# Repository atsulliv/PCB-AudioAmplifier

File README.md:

## Audio Amplifier (AC-DC Converter + Boombox)

This is a complete audio amplification system, integrating an AC–DC power supply with a class D audio amplifier that drives a passive speaker. Implemented rectification, filtering, and voltage regulation (shunting, transistor stage) to convert wall AC into a stable, adjustable DC rail. Designed the amplifier stage to achieve sufficient gain and output power while maintaining signal fidelity and minimizing harmonic distortion. Extended this project by integrates both the converter and amplifier into a single, two-sided PCB.

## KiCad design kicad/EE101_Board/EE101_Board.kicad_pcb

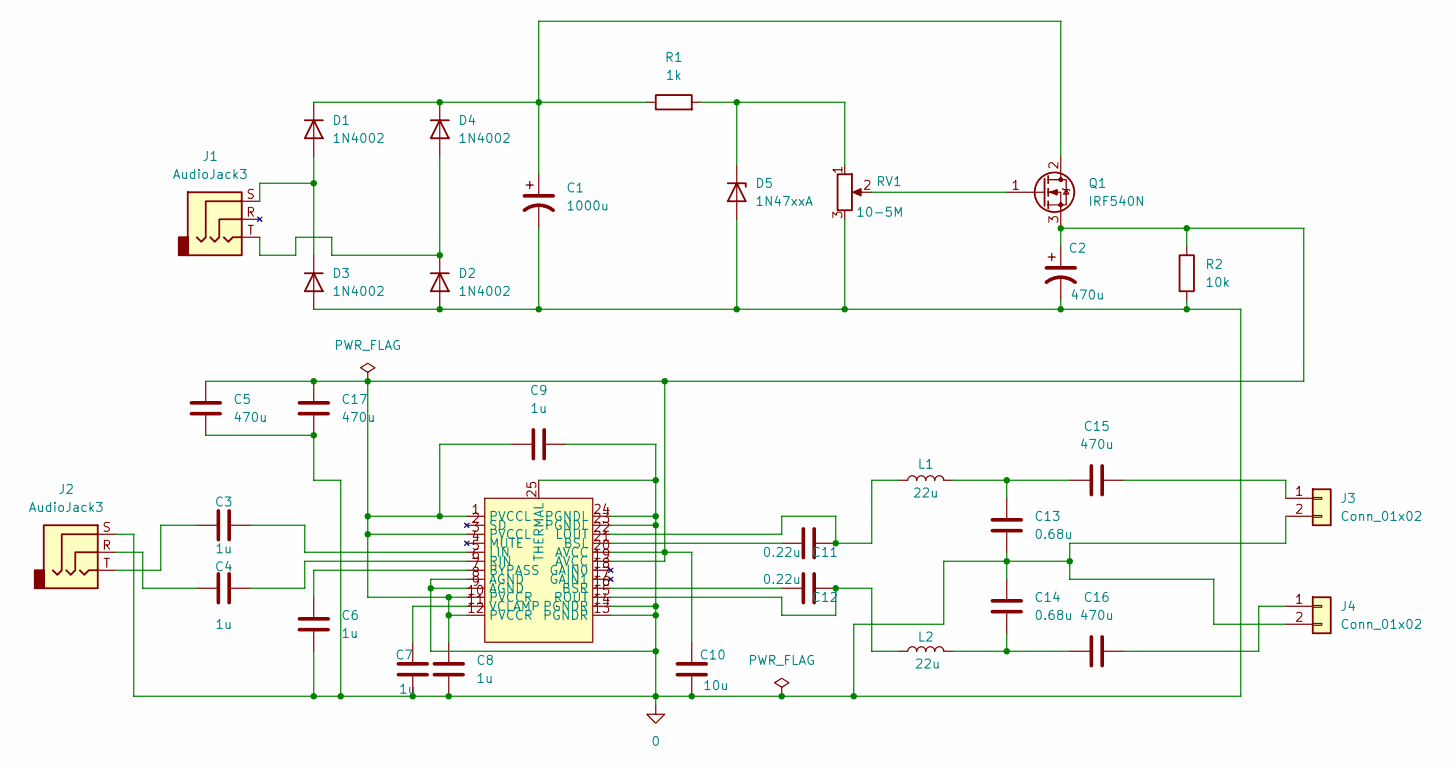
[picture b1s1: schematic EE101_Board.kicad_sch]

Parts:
C1: 1000u; CAPAE1600X1700N
C2: 470u; C-MAL216099003E3
C3, C4, C6, C7, C8, C9: 1u; C_1206_3216Metric_Pad1.33x1.80mm_HandSolder
C5, C15, C16, C17: 470u; Panasonic 25SVPG470M
C10: 10u; C_1206_3216Metric_Pad1.33x1.80mm_HandSolder
C11, C12: 0.22u; C_0603_1608Metric_Pad1.08x0.95mm_HandSolder
C13, C14: 0.68u; C_0805_2012Metric_Pad1.18x1.45mm_HandSolder
D1, D2, D3, D4: 1N4002; D_DO-41_SOD81_P10.16mm_Horizontal
D5: 1N47xxA; DIOM5226X240N
J1, J2: AudioJack3; CUI_SJ-3523-SMT-TR
J3, J4: Conn_01x02; 2249290002
L1, L2: 22u; SRP1038WA220M
Q1: IRF540N; D2PAK-IRF940N
R1: 1k; RESC5025X70N
R2: 10k; R_1206_3216Metric_Pad1.30x1.75mm_HandSolder
RV1: 10-5M; TRIM_3362P-1-205LF
U1: TPA-3123D2-TSSOP - 1.2 mm max height

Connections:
0: C1.2, C2.2, C5.2, C6.2, C7.2, C8.2, C9.2, C10.2, C13.2, C14.1, C17.2, D2.2 (A), D3.2 (A), D5.2 (A), J2.S, J3.2, J4.2, R2.2, RV1.3, U1.8 (AGND), U1.9 (AGND), U1.13 (PGNDR), U1.14 (PGNDR), U1.23 (PGNDL), U1.24 (PGNDL), U1.25 (THERMAL)
unnamed: C3.1, J2.T
unnamed: C4.1, J2.R
unnamed: C13.1, C15.1, L1.2
unnamed: C14.2, C16.1, L2.2
unnamed: D1.2 (A), D3.1 (K), J1.S
unnamed: C1.1, D1.1 (K), D4.1 (K), Q1.2 (D), R1.1
unnamed: D2.1 (K), D4.2 (A), J1.T
unnamed: D5.1 (K), R1.2, RV1.1
unnamed: C15.2, J3.1
unnamed: C16.2, J4.1
unnamed: Q1.1 (G), RV1.2
unnamed: C2.1, C5.1, C8.1, C9.1, C10.1, C17.1, Q1.3 (S), R2.1, U1.1 (PVCCL), U1.3 (PVCCL), U1.10 (PVCCR), U1.12 (PVCCR), U1.19 (AVCC), U1.20 (AVCC)
unnamed: C11.1, U1.21 (BSL)
unnamed: C12.1, U1.16 (BSR)
unnamed: C6.1, U1.7 (BYPASS)
unnamed: C3.2, U1.5 (LIN)
unnamed: C11.2, L1.1, U1.22 (LOUT)
unnamed: C4.2, U1.6 (RIN)
unnamed: C12.2, L2.1, U1.15 (ROUT)
unnamed: C7.1, U1.11 (VCLAMP)

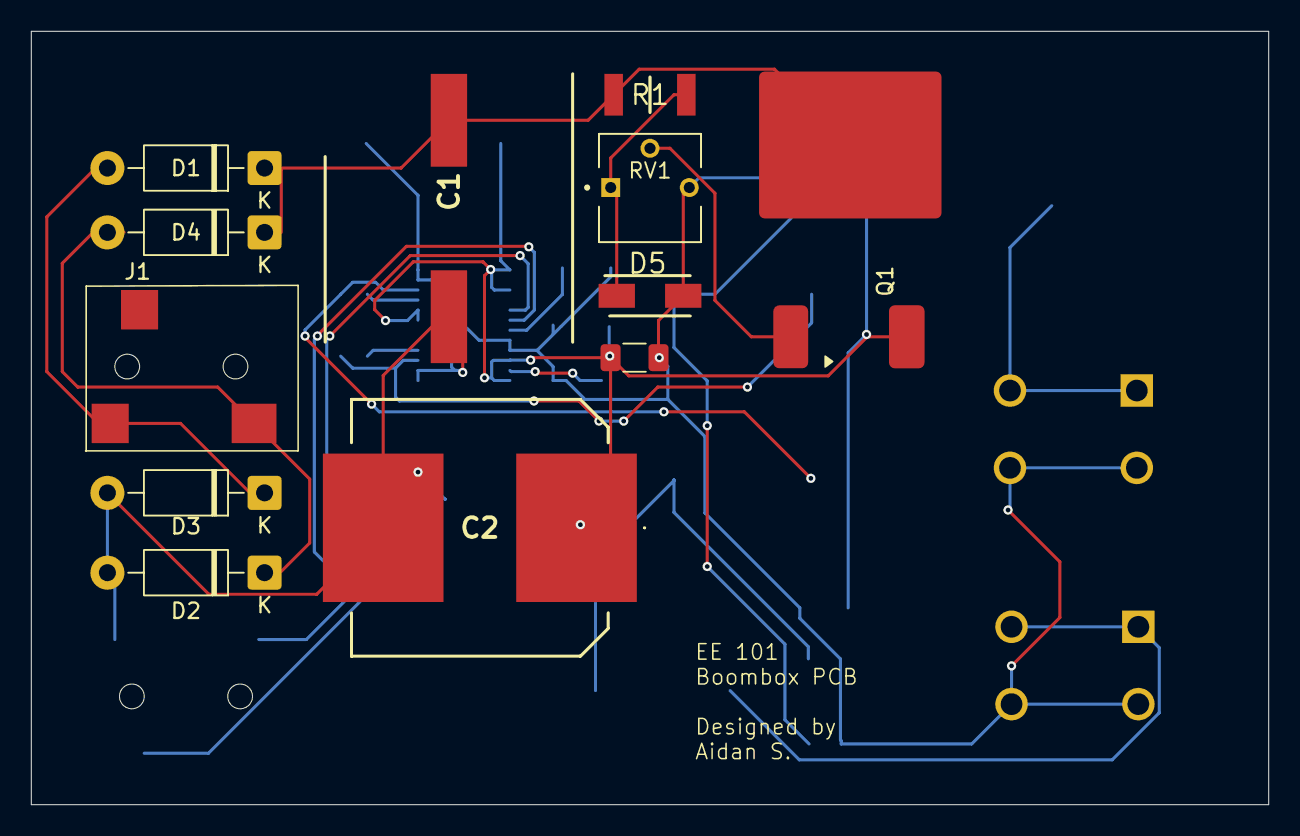
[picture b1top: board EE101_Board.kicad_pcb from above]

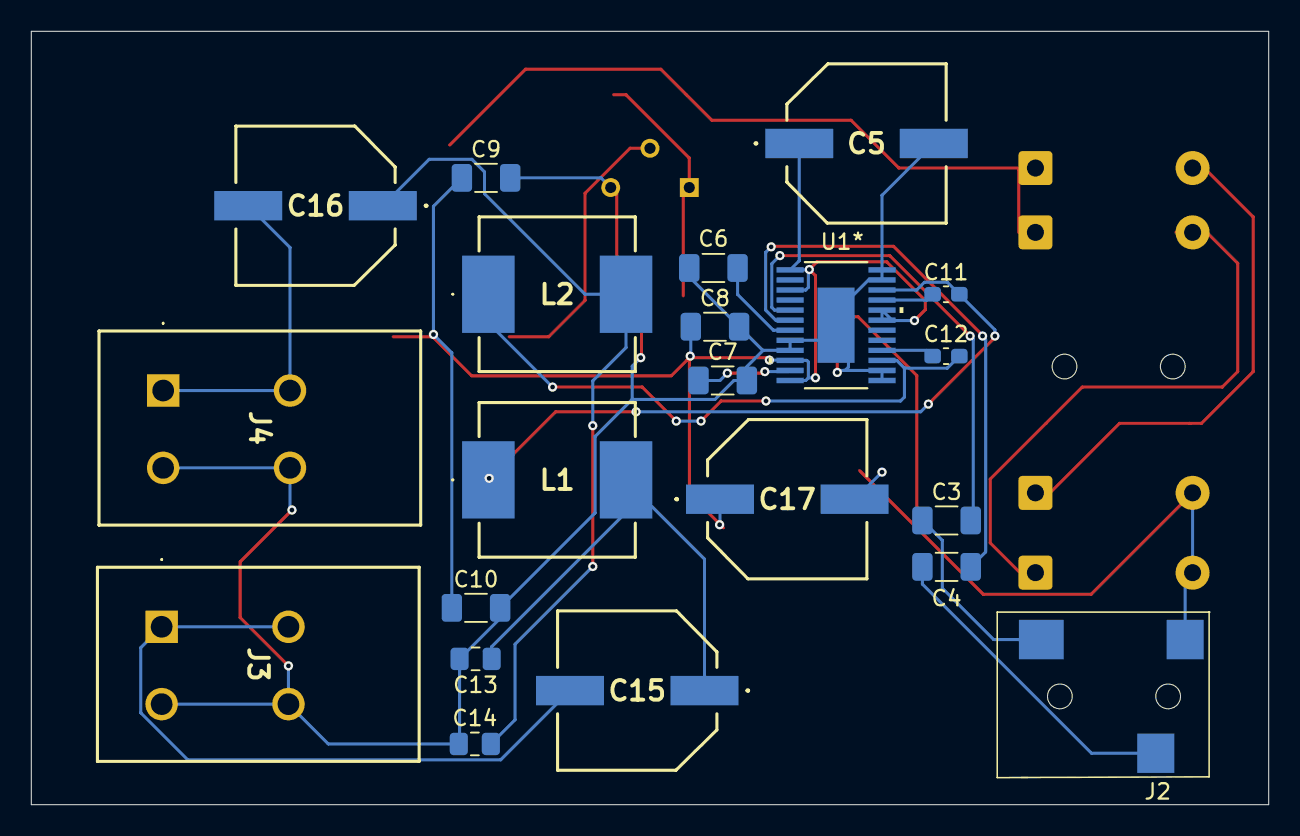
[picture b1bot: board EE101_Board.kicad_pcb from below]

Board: 2 copper layers, 80.0 x 50.0 mm, 33 parts (21 on the bottom side), 21 nets.
